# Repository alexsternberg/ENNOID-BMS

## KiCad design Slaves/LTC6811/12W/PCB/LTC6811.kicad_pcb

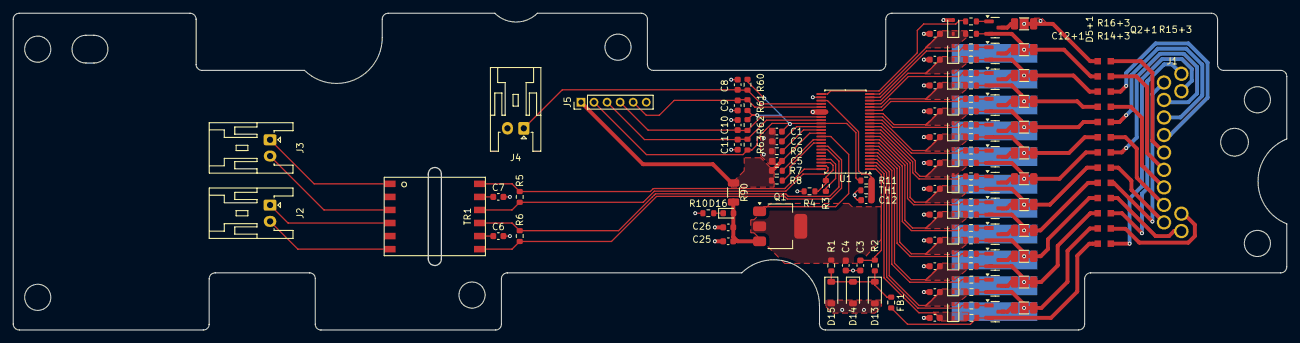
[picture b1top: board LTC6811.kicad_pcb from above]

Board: 2 copper layers, 194.9 x 48.4 mm, 130 parts (1 on the bottom side), 103 nets.

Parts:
C1, C2, C5, C25, C26: 1u; C_0603_1608Metric
C3, C4, C8, C9, C10, C11, C12, C13, C14, C15, C16, C17, C18, C19, C20, C21, C22, C23, C24: 100n; C_0603_1608Metric
C6, C7: 100p; C_0603_1608Metric
D1, D2, D3, D4, D5, D6, D7, D8, D9, D10, D11, D12: PDZ7.5B; D_SOD-323
D13, D14: 1N4148W; D_SOD-123
D15: BZT52H-C62; D_SOD-123
D16: LED; LED_0603_1608Metric
F1, F2, F3, F4, F5, F6, F7, F8, F9, F10, F11, F12, F13: 0.25A; FUSE
FB1: 33; R_0603_1608Metric
J1: Cells; SCiB Header
J2, J3, J4: Conn_01x02; JST_XA_S02B-XASK-1_1x02_P2.50mm_Horizontal
J5: Conn_01x06; PinHeader_1x06_P2.00mm_Vertical
LOGO1: Logo_Open_Hardware_Small; ENNOID-LOGO
Q1: NSV1C201MZ4; SOT-223
Q2, Q3, Q4, Q5, Q6, Q7, Q8, Q9, Q10, Q11, Q12, Q13: TSM2323; SOT-23
R1, R2, R5, R6, R13, R16, R19, R22, R25, R28, R31, R34, R37, R40, R43, R46: 100; R_0603_1608Metric
R3, R10: 1.2k; R_0603_1608Metric
R4: 806; R_0603_1608Metric
R7: 1M; R_0603_1608Metric
R8, R9: 0; R_0603_1608Metric
R11, R60, R61, R62, R63: 100k; R_0603_1608Metric
R12, R15, R18, R21, R24, R27, R30, R33, R36, R39, R42, R45: 36; R_1206_3216Metric
R14, R17, R20, R23, R26, R29, R32, R35, R38, R41, R44, R47: 3.3k; R_0603_1608Metric
R90: 0; R_1206_3216Metric
TH1: 100k; R_0603_1608Metric
TR1: HM2102NL
U1: LTC6811-1; TSSOP-48_6.1x12.5mm_P0.5mm

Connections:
/DRIVE: Q1.1 (B), U1.38 (DRIVE)
/IMA: R6.1, TR1.7, U1.41 (IMA)
/IMB: R5.1, TR1.10, U1.47 (IMB)
/IPA: R6.2, TR1.9, U1.42 (IPA)
/IPB: R5.2, TR1.12, U1.48 (IPB)
/T1: C12.1, R11.2, TH1.1, U1.27 (GPIO1)
/T2: C8.1, J4.1, R60.1, U1.28 (GPIO2)
/T3/GPIO: C9.1, J5.5, R61.1, U1.29 (GPIO3)
/T4/SDA: C10.1, J5.4, R62.1, U1.32 (GPIO4)
/T5/SCL: C11.1, J5.3, R63.1, U1.33 (GPIO5)
/Vref2: C1.1, J5.2, R11.1, R60.2, R61.2, R62.2, R63.2, U1.34 (Vref2)
/Vreg: C5.1, J5.1, R7.2, R8.2, R90.2, U1.37 (Vreg)
/cell1/C: C24.1, D11.2 (A), D12.1 (K), R46.1, U1.24 (C1)
/cell1/C+: F12.2, Q13.2 (S), R42.1, R46.2
/cell1/S: R47.1, U1.25 (S1)
/cell2/C: C23.1, D10.2 (A), D11.1 (K), R43.1, U1.22 (C2)
/cell2/C+: F11.2, Q12.2 (S), R39.1, R43.2
/cell2/S: R44.1, U1.23 (S2)
/cell3/C: C22.1, D9.2 (A), D10.1 (K), R40.1, U1.20 (C3)
/cell3/C+: F10.2, Q11.2 (S), R36.1, R40.2
/cell3/S: R41.1, U1.21 (S3)
/cell4/C: C21.1, D8.2 (A), D9.1 (K), R37.1, U1.18 (C4)
/cell4/C+: F9.2, Q10.2 (S), R33.1, R37.2
/cell4/S: R38.1, U1.19 (S4)
/cell5/C: C20.1, D7.2 (A), D8.1 (K), R34.1, U1.16 (C5)
/cell5/C+: F8.2, Q9.2 (S), R30.1, R34.2
/cell5/S: R35.1, U1.17 (S5)
/cell6/C: C19.1, D6.2 (A), D7.1 (K), R31.1, U1.14 (C6)
/cell6/C+: F7.2, Q8.2 (S), R27.1, R31.2
/cell6/S: R32.1, U1.15 (S6)
/cell7/C: C18.1, D5.2 (A), D6.1 (K), R28.1, U1.12 (C7)
/cell7/C+: F6.2, Q7.2 (S), R24.1, R28.2
/cell7/S: R29.1, U1.13 (S7)
/cell8/C: C17.1, D4.2 (A), D5.1 (K), R25.1, U1.10 (C8)
/cell8/C+: F5.2, Q6.2 (S), R21.1, R25.2
/cell8/S: R26.1, U1.11 (S8)
/cell9/S: R23.1, U1.9 (S9)
/cell10/C: C15.1, D2.2 (A), D3.1 (K), R19.1, U1.6 (C10)
/cell10/C+: F3.2, Q4.2 (S), R15.1, R19.2
/cell10/C-: F4.2, Q5.2 (S), R18.1, R22.2
/cell10/CM: C16.1, D3.2 (A), D4.1 (K), R22.1, U1.8 (C9)
/cell10/S: R20.1, U1.7 (S10)
/cell11/C: C14.1, D1.2 (A), D2.1 (K), R16.1, U1.4 (C11)
/cell11/C+: F2.2, Q3.2 (S), R12.1, R16.2
/cell11/S: R17.1, U1.5 (S11)
/cell12/C: C13.1, D1.1 (K), R13.1, U1.2 (C12)
/cell12/C+: F1.2, FB1.2, Q2.2 (S), R13.2
/cell12/S: R14.1, U1.3 (S12)
GND: C1.2, C2.2, C3.2, C4.2, C5.2, C6.2, C7.2, C8.2, C9.2, C10.2, C11.2, C12.2, C13.2, C14.2, C15.2, C16.2, C17.2, C18.2, C19.2, C20.2, C21.2, C22.2, C23.2, C24.2, C25.2, C26.2, D12.2 (A), D13.2 (A), D14.2 (A), D15.2 (A), F13.2, J4.2, J5.6, R4.2, R9.2, R10.2, R45.1, TH1.2, U1.26 (C0), U1.30 (V-**), U1.31 (V-)
unnamed: C4.1, Q1.2 (C), Q1.4 (C), R1.2
unnamed: C6.1, TR1.8
unnamed: C7.1, TR1.11
unnamed: D13.1 (K), D14.1 (K), D15.1 (K), FB1.1, R1.1, R2.1
unnamed: C25.1, C26.1, D16.2 (A), Q1.3 (E), R90.1
unnamed: D16.1 (K), R10.1
unnamed: F13.1, J1.1
unnamed: F12.1, J1.2
unnamed: F11.1, J1.3
unnamed: F10.1, J1.4
unnamed: F9.1, J1.5
unnamed: F8.1, J1.6
unnamed: F7.1, J1.7
unnamed: F6.1, J1.8
unnamed: F5.1, J1.9
unnamed: F4.1, J1.10
unnamed: F3.1, J1.11
unnamed: F2.1, J1.12
unnamed: F1.1, J1.13
unnamed: J2.1, TR1.4
unnamed: J2.2, TR1.6
unnamed: J3.1, TR1.1
unnamed: J3.2, TR1.3
unnamed: Q2.3 (D), R12.2
unnamed: Q2.1 (G), R14.2
unnamed: Q3.3 (D), R15.2
unnamed: Q3.1 (G), R17.2
unnamed: Q4.3 (D), R18.2
unnamed: Q4.1 (G), R20.2
unnamed: Q5.3 (D), R21.2
unnamed: Q5.1 (G), R23.2
unnamed: Q6.3 (D), R24.2
unnamed: Q6.1 (G), R26.2
unnamed: Q7.3 (D), R27.2
unnamed: Q7.1 (G), R29.2
unnamed: Q8.3 (D), R30.2
unnamed: Q8.1 (G), R32.2
unnamed: Q9.3 (D), R33.2
unnamed: Q9.1 (G), R35.2
unnamed: Q10.3 (D), R36.2
unnamed: Q10.1 (G), R38.2
unnamed: Q11.3 (D), R39.2
unnamed: Q11.1 (G), R41.2
unnamed: Q12.3 (D), R42.2
unnamed: Q12.1 (G), R44.2
unnamed: Q13.3 (D), R45.2
unnamed: Q13.1 (G), R47.2
unnamed: R9.1, U1.36 (DTEN)
unnamed: R3.1, U1.45 (IBIAS)
unnamed: R3.2, R4.1, U1.46 (ICMP)
unnamed: R8.1, U1.40 (ISOMD)
unnamed: C3.1, R2.2, U1.1 (V+)
unnamed: C2.1, U1.35 (Vref1)
unnamed: R7.1, U1.39 (WDT)

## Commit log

2024-10-24 Add Honda SCiB module PCB
2024-10-26 Add PCB
2024-10-26 finish balancing
2024-11-24 Finish most routing
2024-11-30 Finish Rev1
2025-04-09 more updates
